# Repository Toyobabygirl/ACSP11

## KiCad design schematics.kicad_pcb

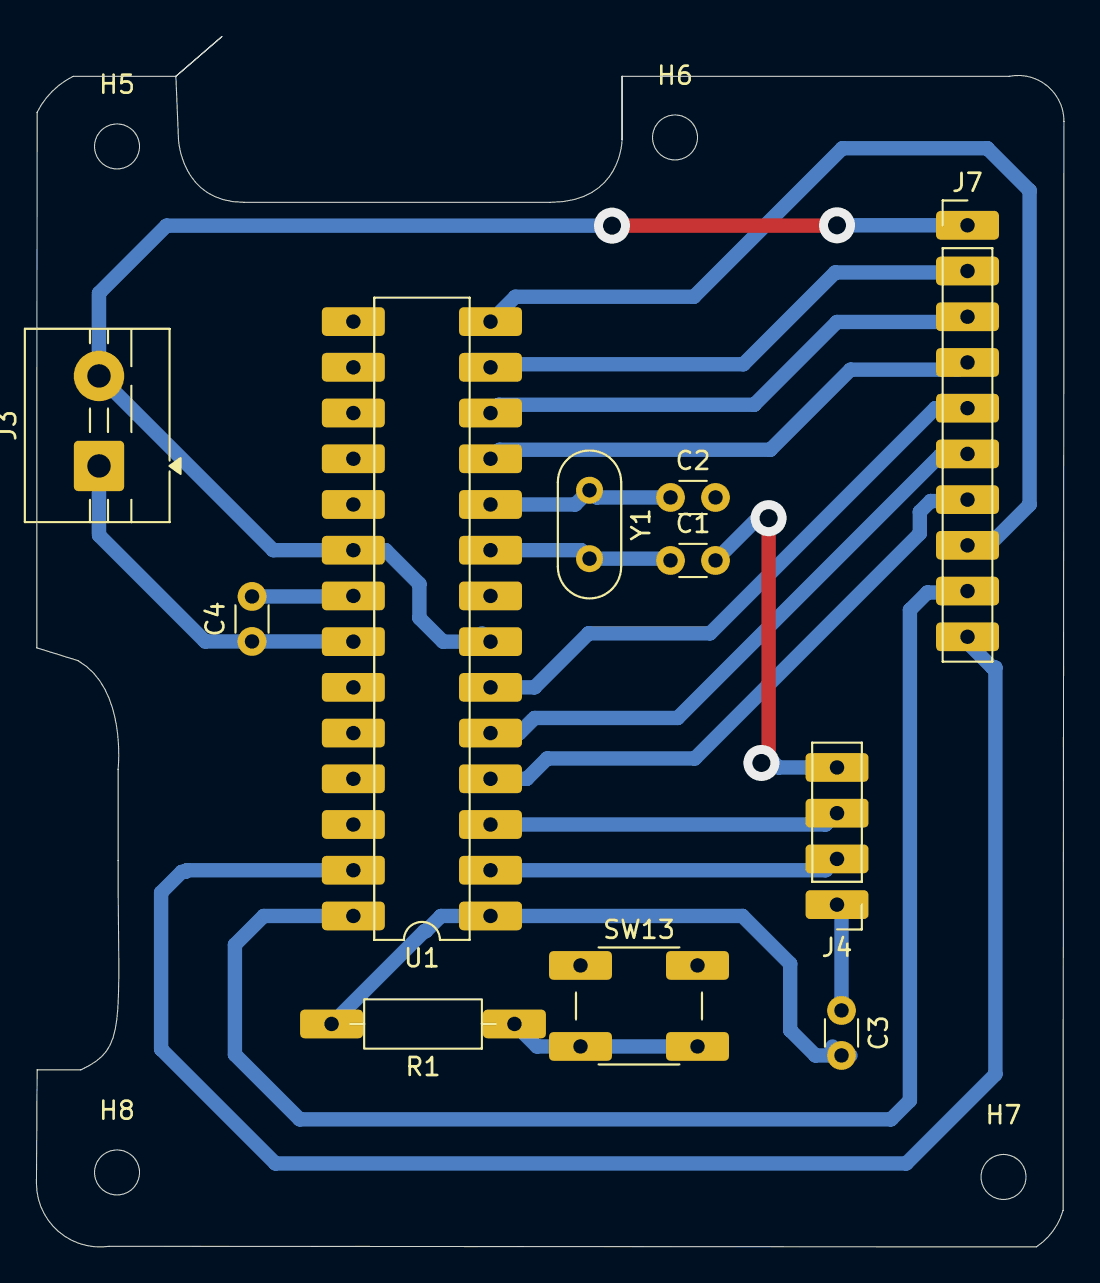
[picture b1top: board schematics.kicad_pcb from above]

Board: 2 copper layers, 57.1 x 67.3 mm, 15 parts (0 on the bottom side), 19 nets.

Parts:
C1, C2, C3, C4: C; C_Disc_D3.0mm_W1.6mm_P2.50mm
H5, H6, H7, H8: MountingHole; MountingHole_2.5mm
J3: Screw_Terminal_01x02; TerminalBlock_MaiXu_MX126-5.0-02P_1x02_P5.00mm
J4: Conn_01x04_Pin; PinHeader_1x04_P2.54mm_Vertical
J7: Conn_01x10_Pin; PinHeader_1x10_P2.54mm_Vertical
R1: 10k; R_Axial_DIN0207_L6.3mm_D2.5mm_P10.16mm_Horizontal
SW13: SW_Push; SW_PUSH_6mm
U1: ATmega328P-P; DIP-28_W7.62mm
Y1: Crystal; Crystal_HC52-6mm_Vertical

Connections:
+5V: J3.2, J7.1, U1.7 (VCC), U1.20 (AVCC)
GND: C1.2, C2.2, C4.1, J3.1, J4.4, SW13.1, U1.8 (GND), U1.22 (GND)
unnamed: C3.1, J4.1
unnamed: J4.2, U1.2 (PD0)
unnamed: J4.3, U1.3 (PD1)
unnamed: J7.2, U1.13 (PD7)
unnamed: J7.3, U1.12 (PD6)
unnamed: J7.4, U1.11 (PD5)
unnamed: J7.5, U1.6 (PD4)
unnamed: J7.6, U1.5 (PD3)
unnamed: J7.7, U1.4 (PD2)
unnamed: J7.8, U1.14 (PB0)
unnamed: J7.9, U1.28 (PC5)
unnamed: J7.10, U1.27 (PC4)
unnamed: R1.1, SW13.2
unnamed: C4.2, U1.21 (AREF)
unnamed: C1.1, U1.9 (XTAL1/PB6), Y1.2
unnamed: C2.1, U1.10 (XTAL2/PB7), Y1.1
unnamed: C3.2, R1.2, U1.1 (~RESET/PC6)

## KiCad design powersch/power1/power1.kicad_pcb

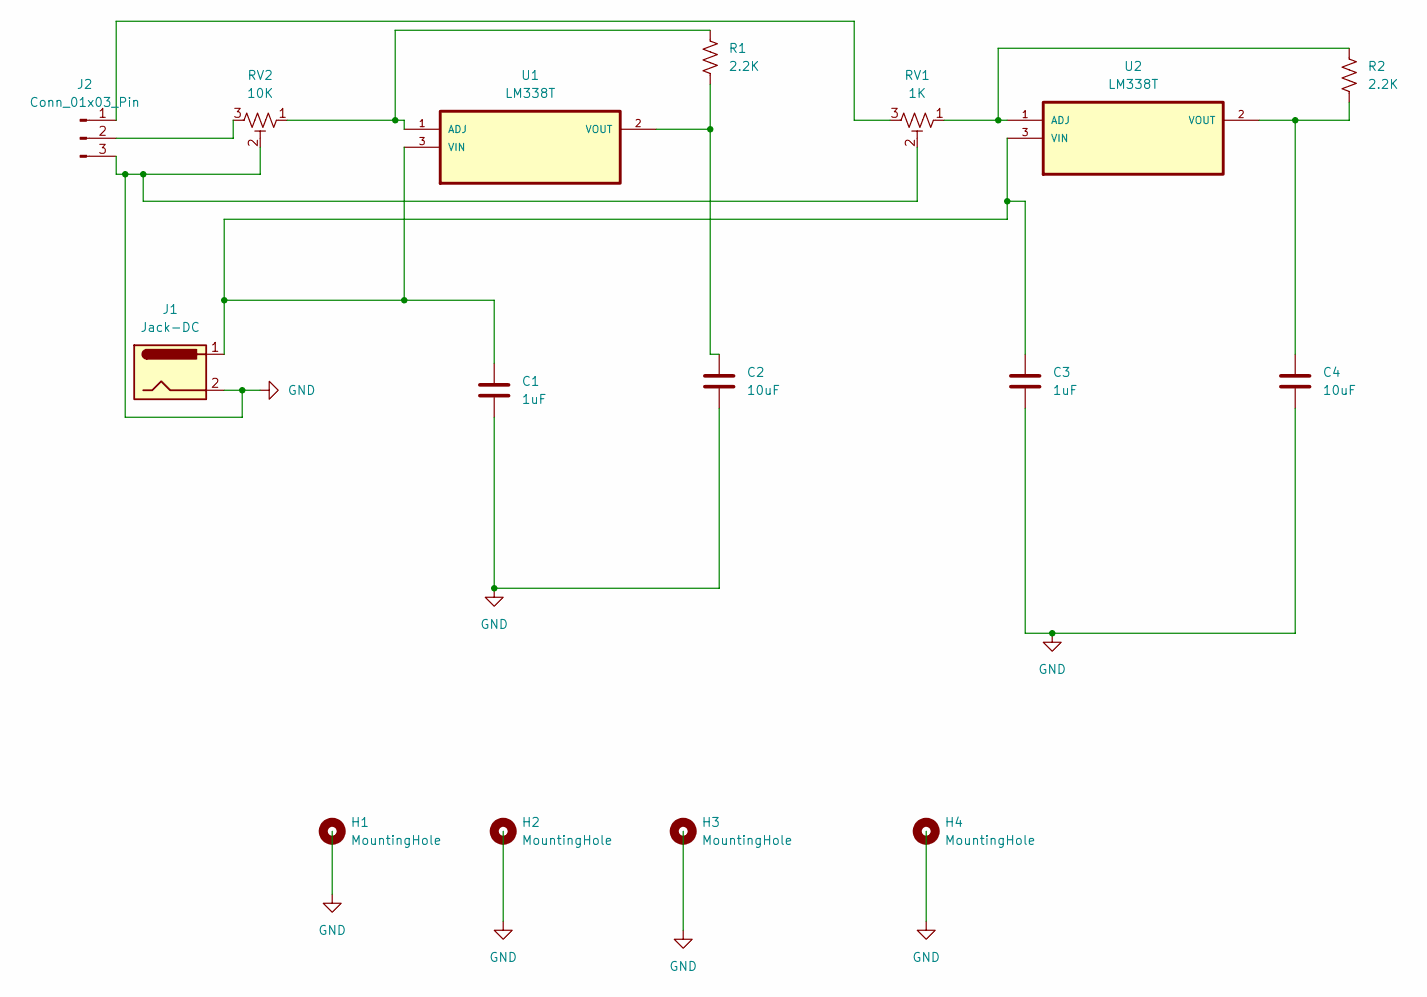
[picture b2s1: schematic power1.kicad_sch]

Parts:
C1, C3: 1uF; CP_Radial_D5.0mm_P2.00mm
C2, C4: 10uF; CP_Radial_D6.3mm_P2.50mm
H1, H2, H3, H4: MountingHole; MountingHole_2.5mm
J1: Jack-DC; BarrelJack_CUI_PJ-102AH_Horizontal
J2: Conn_01x03_Pin; PinHeader_1x03_P2.54mm_Vertical
R1, R2: 2.2K; R_Axial_DIN0207_L6.3mm_D2.5mm_P7.62mm_Horizontal
RV1: 1K; Potentiometer_Alpha_RD901F-40-00D_Single_Vertical_CircularH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
RV2: 10K; Potentiometer_Alpha_RD901F-40-00D_Single_Vertical_CircularH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
U1, U2: LM338T; TO-220-3_Vertical

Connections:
GND: C1.2, C2.2, C3.2, C4.2, J1.2, J2.3, RV1.2, RV2.2
unnamed: J2.1, RV1.3
unnamed: J2.2, RV2.3
unnamed: R1.1, RV2.1, U1.1 (ADJ)
unnamed: C1.1, C3.1, J1.1, U1.3 (VIN), U2.3 (VIN)
unnamed: C2.1, R1.2, U1.2 (VOUT)
unnamed: R2.1, RV1.1, U2.1 (ADJ)
unnamed: C4.1, R2.2, U2.2 (VOUT)

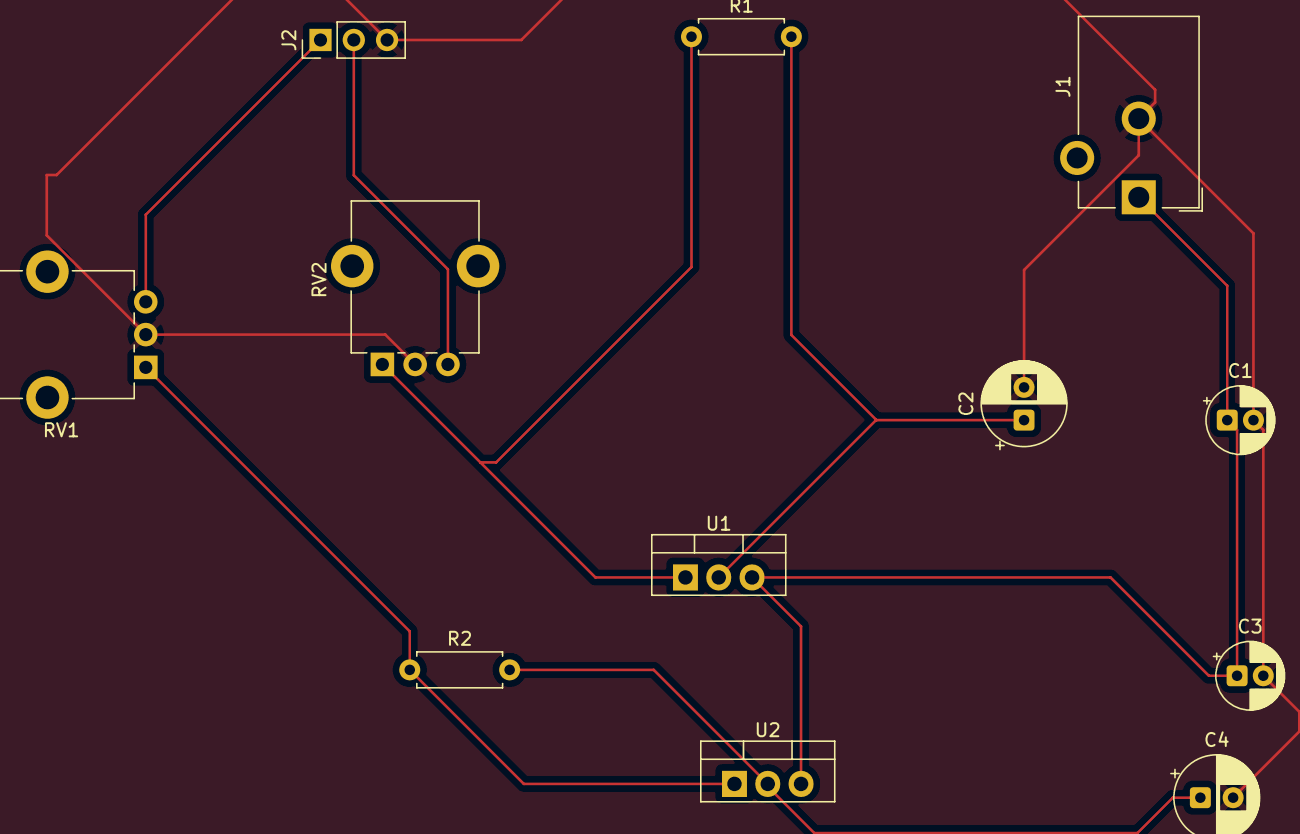
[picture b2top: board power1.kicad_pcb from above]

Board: 2 copper layers, 16 parts (0 on the bottom side), 8 nets.

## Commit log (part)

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2025-11-13 schematics added
2026-03-10 ACSC
